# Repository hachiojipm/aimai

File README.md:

(Japanese doc is here: [README_ja](./README_ja.md))

aimai is an "FM transceiver" name tag based on ESP32.

## Features

- FM radio receiver
  - Receiving sound
  - Receiving text data with [Radio Data System (RDS)](https://wikipedia.org/wiki/Radio_Data_System)
- FM radio transmitter
  - Transmitting sound
  - Transmitting text data with RDS
- Write your name on the board :)

## How to use

### Receiving (RX mode)

HIGHLY RECOMMENDED: it should be plugged earphones into the RX module's (purple one) phone jack because the earphones line works as an antenna. If not, it might be not able to receive text data through RDS.

- Turn on the device (by toggle switch at the top of left)
- Switch to the RX mode (by toggle switch at the top of right)
- The left knob: adjust the loudness
- The right knob: adjust the RX frequency
- OLED display: it shows received text data

### Transmitting (TX mode)

- Turn on the device (by toggle switch at the top of left)
- Switch to the TX mode (by toggle switch at the top of right)
- This mode transmits sound data through the TX module (the right one) line
- The left knob: RDS text input
  - Turn the knob, it chooses the characters
  - Click the knob, it decides a character
  - It needs to input 20 characters (hint: it supports the space character)
- The right knob: adjust the TX frequency
  - Click the knob, this is an escape key (i.e. leave from text input mode)
- OLED display: it shows transmitting text data

## How to build and upload the binary to ESP32 board

### Requirements

- [pythonz](https://github.com/saghul/pythonz)
- [direnv](https://github.com/direnv/direnv)

### How to bootstrap the project

```
$ make bootstrap
```

### How to build

```
$ make build
```

### How to upload

```
$ make upload
```

If you have something trouble, please edit the `upload_port` configuration on [platformio.ini](./platformio.ini).

## How to construct the board

A schematic and PCB data are here: [pcb](./pcb)

## Note

This project is optimized for Japan coverage. If you would like to use this device in countries other than Japan, you should modify the code of frequency band for `Si4703` and `Si4713`.

## Makers

- [uzulla](https://github.com/uzulla)
- [mackee](https://github.com/mackee)
- [moznion](https://github.com/moznion)

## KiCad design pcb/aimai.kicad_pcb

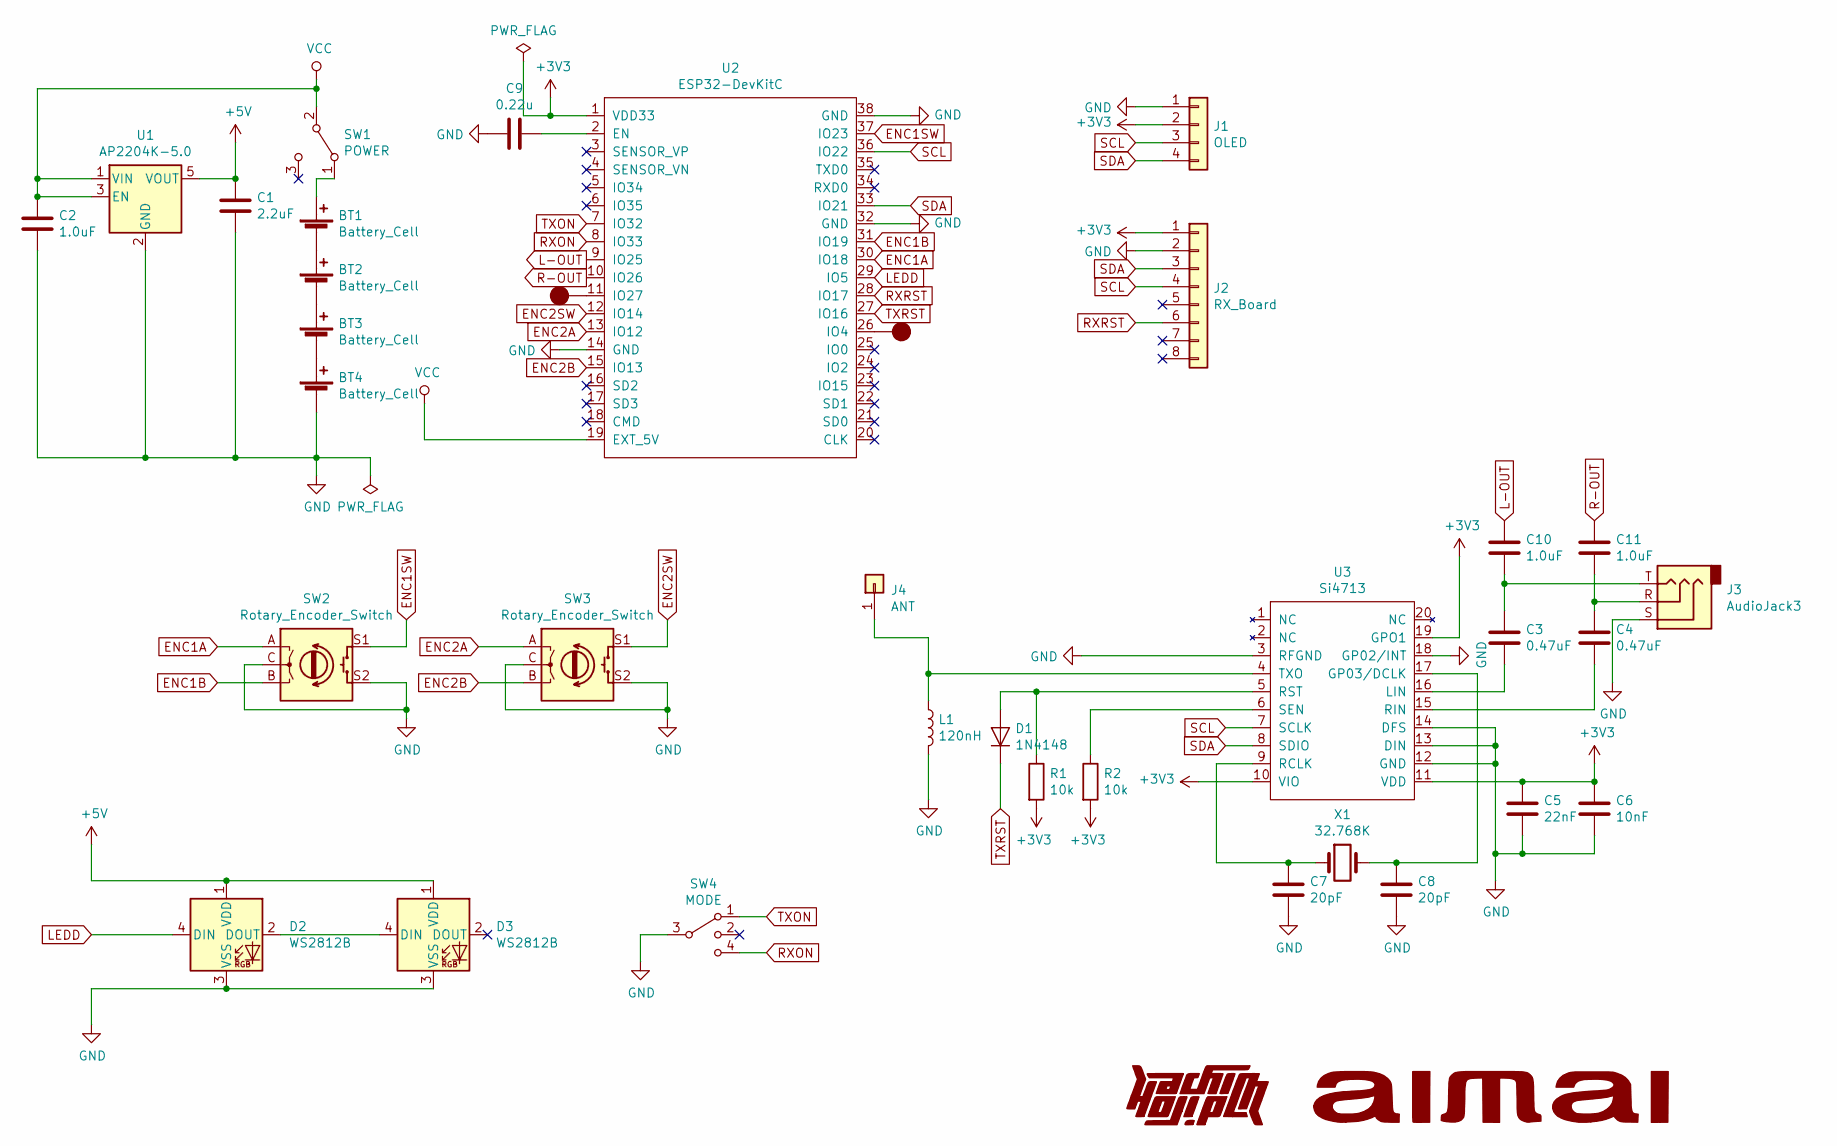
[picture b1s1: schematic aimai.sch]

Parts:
BT1, BT2, BT3, BT4: Battery_Cell; AAA-holder
C1: 2.2uF; C_0402
C2, C10, C11: 1.0uF; C_0402
C3, C4: 0.47uF; C_0402
C5: 22nF; C_0603
C6: 10nF; C_0603
C7, C8: 20pF; C_0603
C9: 0.22u; C_0603
D1: 1N4148; D_SOD-123
D2, D3: WS2812B; LED_WS2812B_PLCC4_5.0x5.0mm_P3.2mm
J1: OLED; SSD1306-128x32-Module
J2: RX_Board; Si4703-Module
J3: AudioJack3; ST-005-G
J4: ANT; Pin_Header_Straight_1x01_Pitch2.54mm
L1: 120nH; Neosid_Inductor_SM0603CG
R1, R2: 10k; C_0603
SW1: POWER; SW_SPDT_PCM12
SW2, SW3: Rotary_Encoder_Switch; RotaryEncoder_Alps_EC12E-Switch_Vertical_H20mm
SW4: MODE; SW_SP3T_PCM13
TOUCH1, TOUCH2: touchpad
U1: AP2204K-5.0; SOT-23-5
U2: ESP32-DevKitC
U3: Si4713; SiliconLabs_QFN-20-1EP_3x3mm_Pitch0.5mm
X1: 32.768K; Crystal_SMD_3215-2pin_3.2x1.5mm

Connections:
+3V3: C5.1, C6.1, J1.2, J2.1, R1.2, R2.2, U2.1 (VDD33), U3.10 (VIO), U3.11 (VDD), U3.19 (GPO1)
+5V: C1.1, D2.1 (VDD), D3.1 (VDD), U1.5 (VOUT)
ENC1A: SW2.A, U2.30 (IO18)
ENC1B: SW2.B, U2.31 (IO19)
ENC1SW: SW2.S1, U2.37 (IO23)
ENC2A: SW3.A, U2.13 (IO12)
ENC2B: SW3.B, U2.15 (IO13)
ENC2SW: SW3.S1, U2.12 (IO14)
GND: BT4.2 (-), C1.2, C2.2, C5.2, C6.2, C7.2, C8.2, C9.2, D2.3 (VSS), D3.3 (VSS), J1.1, J2.2, J3.S, L1.2, SW2.C, SW2.S2, SW3.C, SW3.S2, SW4.3, U1.2 (GND), U2.14 (GND), U2.32 (GND), U2.38 (GND), U3.3 (RFGND), U3.12 (GND), U3.13 (DIN), U3.14 (DFS), U3.18 (GP02/INT)
L-OUT: C10.1, U2.9 (IO25)
LEDD: D2.4 (DIN), U2.29 (IO5)
unnamed: BT1.1 (+), SW1.1 (A)
unnamed: BT1.2 (-), BT2.1 (+)
unnamed: BT2.2 (-), BT3.1 (+)
unnamed: BT3.2 (-), BT4.1 (+)
unnamed: C3.2, U3.16 (LIN)
unnamed: C4.2, U3.15 (RIN)
unnamed: C7.1, U3.9 (RCLK), X1.1
unnamed: C8.1, U3.17 (GP03/DCLK), X1.2
unnamed: C9.1, U2.2 (EN)
unnamed: C3.1, C10.2, J3.T
unnamed: C4.1, C11.2, J3.R
unnamed: D1.2 (A), R1.1, U3.5 (RST)
unnamed: D2.2 (DOUT), D3.4 (DIN)
unnamed: J4.1, L1.1, U3.4 (TXO)
unnamed: R2.1, U3.6 (SEN)
unnamed: TOUCH1.~, U2.26 (IO4)
unnamed: TOUCH2.~, U2.11 (IO27)
R-OUT: C11.1, U2.10 (IO26)
RXON: SW4.4, U2.8 (IO33)
RXRST: J2.6, U2.28 (IO17)
SCL: J1.3, J2.4, U2.36 (IO22), U3.7 (SCLK)
SDA: J1.4, J2.3, U2.33 (IO21), U3.8 (SDIO)
TXON: SW4.1, U2.7 (IO32)
TXRST: D1.1 (K), U2.27 (IO16)
VCC: C2.1, SW1.2 (B), U1.1 (VIN), U1.3 (EN), U2.19 (EXT_5V)

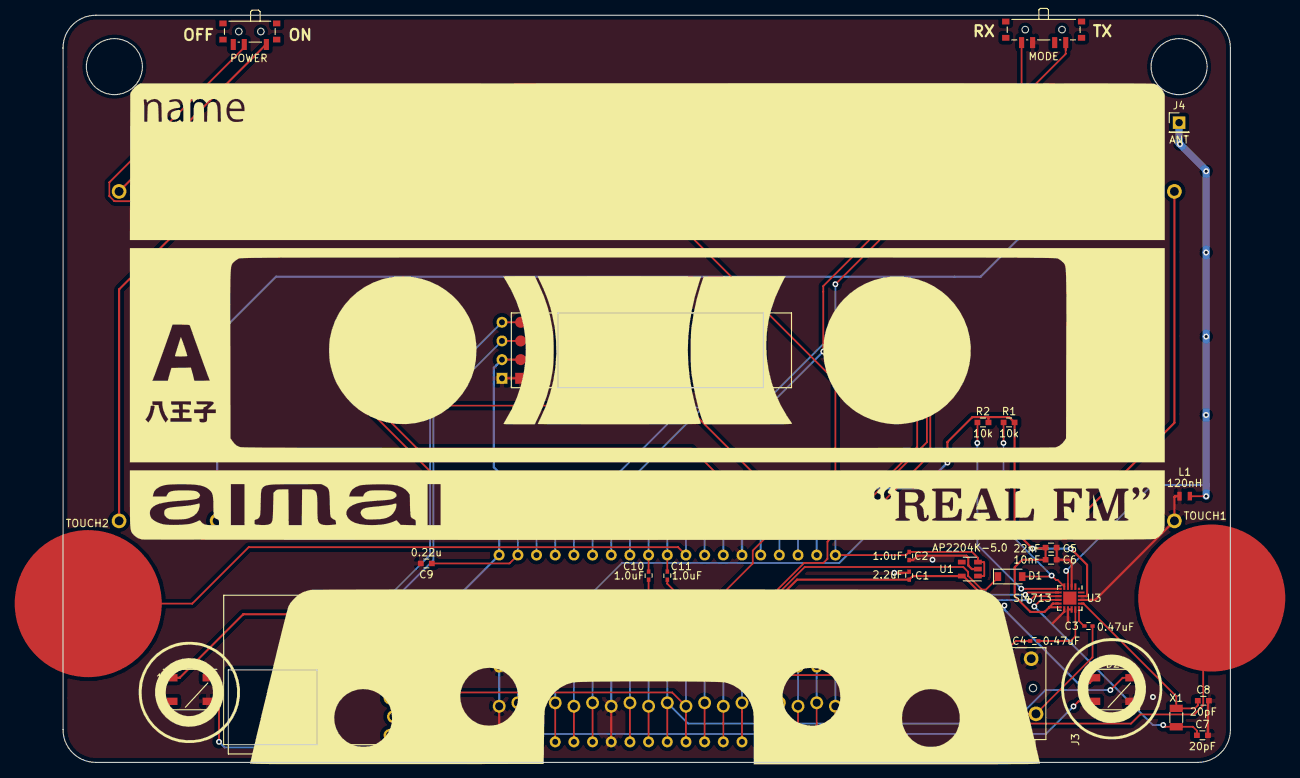
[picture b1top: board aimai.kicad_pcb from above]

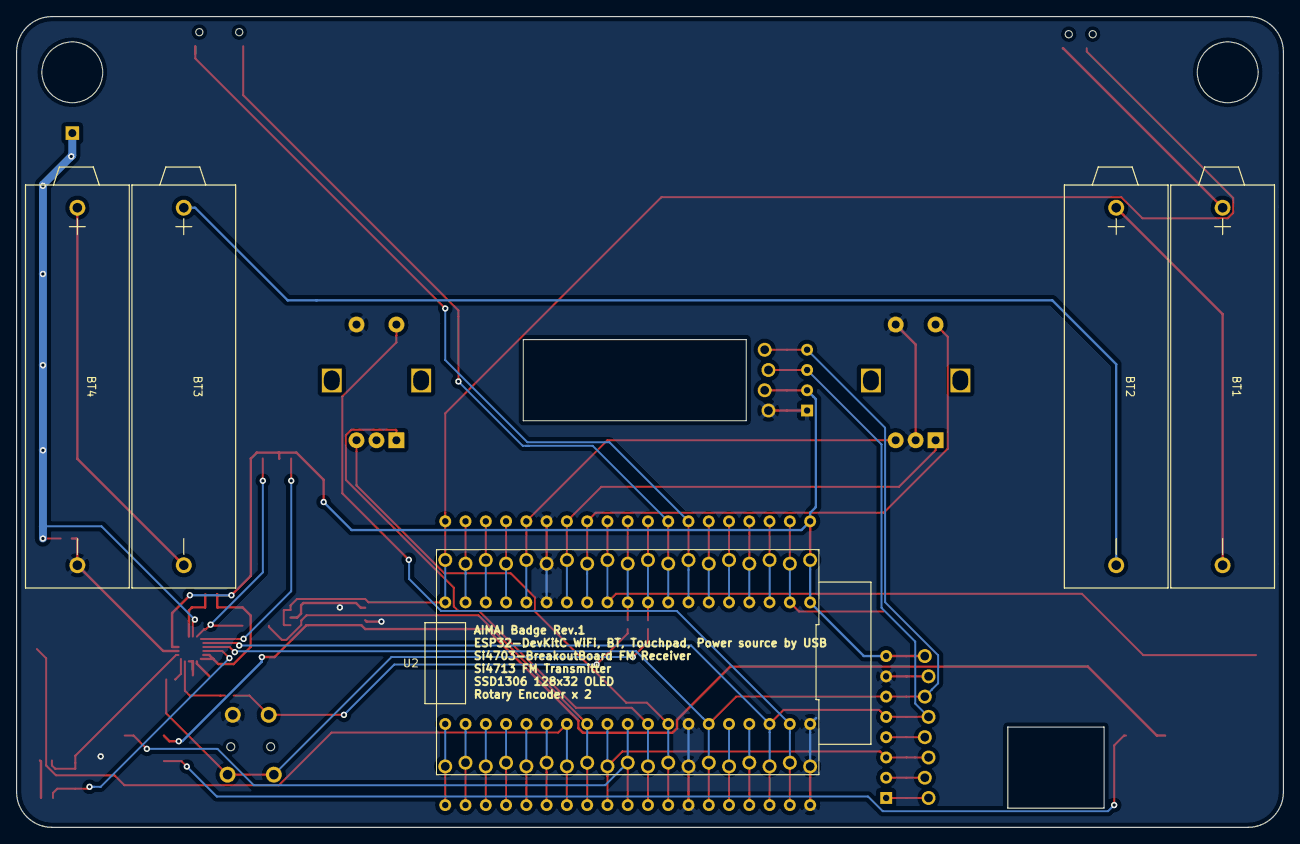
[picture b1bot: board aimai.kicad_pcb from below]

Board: 2 copper layers, 158.8 x 101.6 mm, 37 parts (6 on the bottom side), 36 nets.

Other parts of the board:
G1: LOGO; awia_silk
G2: LOGO; awia_silk_back

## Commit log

2019-08-12 Introduce the platformio
2019-08-12 Add dependency for Si4703
2019-08-12 Adjust rotary pin number
2019-08-12 Support rx (sound only)
2019-08-12 Add rotary encoder's sw pin definitions
2019-08-12 Rename the ambiguous instance name
2019-08-12 Support RDS
2019-08-12 Support TX freq changing
2019-08-12 Use function pointer for main loop's mode selecting
2019-08-12 Add some definitions for each function into the header file
2019-08-12 Support action mode switching
2019-08-12 Tidy up the constants
2019-08-12 Invert the position of the rotary switches
2019-08-12 Make it to be able to input the RDS text (and to escape from it)
2019-08-13 Support reading RDS information periodically
2019-08-13 Show splash text on the LED
2019-08-14 Add SSD1306 dependency
2019-08-14 Add the Si4713 dep
2019-08-14 Add script for development to put symlinks for libs
2019-08-20 Swap RX/TX mode pins
2019-08-20 Fix to use the CORRECT SSD1306 library
2019-08-20 Separate main task and RDS text listening task by physical CPU core
2019-08-21 Render the logo image
2019-08-21 Fix the function name
2019-08-21 Add OLED viewing logic for RX freq and vol
2019-08-21 Prepare the displaying RDS
2019-08-21 Simplify the rx/tx initializing on initial loop
2019-08-21 Simplify!!
2019-08-21 Implement simple marquee
2019-08-22 Implement RX RDS marquee
2019-08-22 Kick out OLED logics to the external
2019-08-28 Fix OLED resolution
2019-08-28 Show tx freq on OLED
2019-08-28 dbg log
2019-08-28 Add workaround for chattering on RDS text entering
2019-08-28 Implement user interface to input RDS text
2019-08-29 Reduce the risk of crashing
2019-08-30 Fix declare modifier
2019-08-30 Show tx rds text
2019-08-30 Remember the tx RDS text
2019-08-31 Support RDS text receiving
2019-09-03 add schematics, pcb
2019-09-17 :pencil: doc
2019-09-17 add dep
2019-09-18 Fix bootstrap script
    Add git submodule initializing
2019-09-18 :pencil: add bootstrapping procedure
2019-09-18 :pencil: fix required tools
